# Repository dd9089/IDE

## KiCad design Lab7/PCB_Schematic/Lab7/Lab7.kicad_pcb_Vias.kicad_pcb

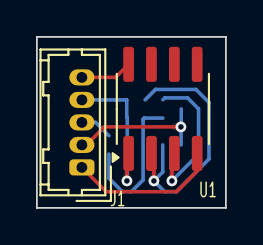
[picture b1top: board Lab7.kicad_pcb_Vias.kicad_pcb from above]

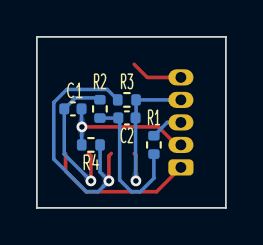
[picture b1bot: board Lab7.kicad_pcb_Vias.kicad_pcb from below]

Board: 2 copper layers, 10.5 x 9.5 mm, 8 parts (6 on the bottom side), 8 nets.

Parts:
C1: 1.36u; C_0402_1005Metric
C2: 0.68u; C_0402_1005Metric
J1: Conn_01x05_Pin; Hirose_DF13-05P-1.25DSA_1x05_P1.25mm_Vertical
R1: 7k; R_0402_1005Metric
R2: 40k; R_0402_1005Metric
R3: 480k; R_0402_1005Metric
R4: 54k; R_0402_1005Metric
U1: TLC277; SOIC-8_3.9x4.9mm_P1.27mm

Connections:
/+15V0: J1.5, U1.8 (V+)
/-15V0: J1.1, U1.4 (V-)
/Vin: J1.3, R1.1
/Vout: C2.2, J1.4, R3.2, U1.1
GND: C1.2, J1.2, R4.1
unnamed: C2.1, R1.2, R2.1
unnamed: C1.1, R2.2, U1.3 (+)
unnamed: R3.1, R4.2, U1.2 (-)

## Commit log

2025-02-21 Add files via upload
    added project file and main
2025-02-21 added project file to github
2025-02-21 fixed some configuration settings
2025-02-21 added rest of files
2025-02-21 fixing some errors
2025-02-21 Project Configuration Settings
2025-02-21 Added Common.h
2025-02-21 Changed HEAP and clk speed
2025-02-21 Added LED, Switch, UART init files
2025-02-21 Renamed LED to leds as the main file requires
2025-02-21 deleted the extranious main file
2025-02-23 Worked on ADC14 main file
2025-02-24 Finished ADC14.c
2025-02-24 removed the project files from git
2025-02-24 Lab5-Timer, switches init, uart init
2025-02-24 almost done with part 2
2025-02-24 finished part 2?
2025-02-24 Timer and switch interrupts working, full implementation incomplete
2025-02-25 Conditional in main to account for switch presses.
2025-02-25 finished part 2
2025-02-25 Part 2 is signed off
2025-02-26 Lab (Part1) Timer/LED functionality (sw1 complete, sw2 almost done)
2025-02-26 Part 1 switch timers complete.
2025-02-26 Started Part 3
2025-02-26 finsihed part 3?
2025-02-27 added screenshots and finished part 3
2025-02-27 added more screenshots for part 2
2025-02-28 Create whyu
2025-02-28 Create why
2025-02-28 added given files from gitlab
2025-02-28 added dependencies from previous labs
2025-02-28 Added pwm init and duty cycle modulation to Lab6-DCMotor
2025-03-06 TimerA.c implementation (incomplete)
2025-03-07 Part 1 is done. Error was wrong pin connection and did not init second pin `# modified: Lab06.uvoptx
2025-03-12 May have finished Part 3 needs to be checked with a servo Also needs TA signoff
2025-03-12 Mightve finished part 4 needs to be checked if part 3 doesnt work this wont either
2025-03-12 Servo motors work with code :) just need TA signoffs for parts 3 and 4
2025-03-26 Finished Lab 7 need a signoff
2025-03-26 fixed some cosmetic issues
2025-03-27 Got signoffs
2025-03-28 Added the screen shots
2025-03-28 Actually added the screen shots
2025-03-28 Added slopes to the c-gradiant passive filter
2025-03-28 Added the PCB files
2025-03-28 Forgot the PCB Screen Shots
2025-03-28 hope this works now
2025-04-02 added car project repo servo somewhat works need to tune the left, right, center parameters camera works oled works motors dont work, pwm is sent to out pins cant read it from the connection to motor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
2025-04-02 motors work caer seems drunk
2025-04-02 added some possibilities to make car turn faster changed the clock speed might want to change servo period changed the delay time in main, do we want a delay?
2025-04-04 Bluetooth incorporated, needs some tweaking
2025-04-06 our little boy Justin is finally drunk driving :)
2025-04-06 forgot to add some files
2025-04-09 Modified the steering code got rid of all warnings
2025-04-10 Sorta works, ended up randomly stopping
2025-04-10 milestone 2 works
2025-04-11 Added PID Contoller. Might not work
2025-04-11 got rid of the warnings now uses servo_turn(float) instead of right left and center functions
2025-04-21 pid works most of the time need to fine tune it still
2025-04-21 PID does not work fix it
2025-04-22 WORKS need to make it faster
2025-04-26 works need to see if going slower might be better.
2025-04-26 Final code hopefully
